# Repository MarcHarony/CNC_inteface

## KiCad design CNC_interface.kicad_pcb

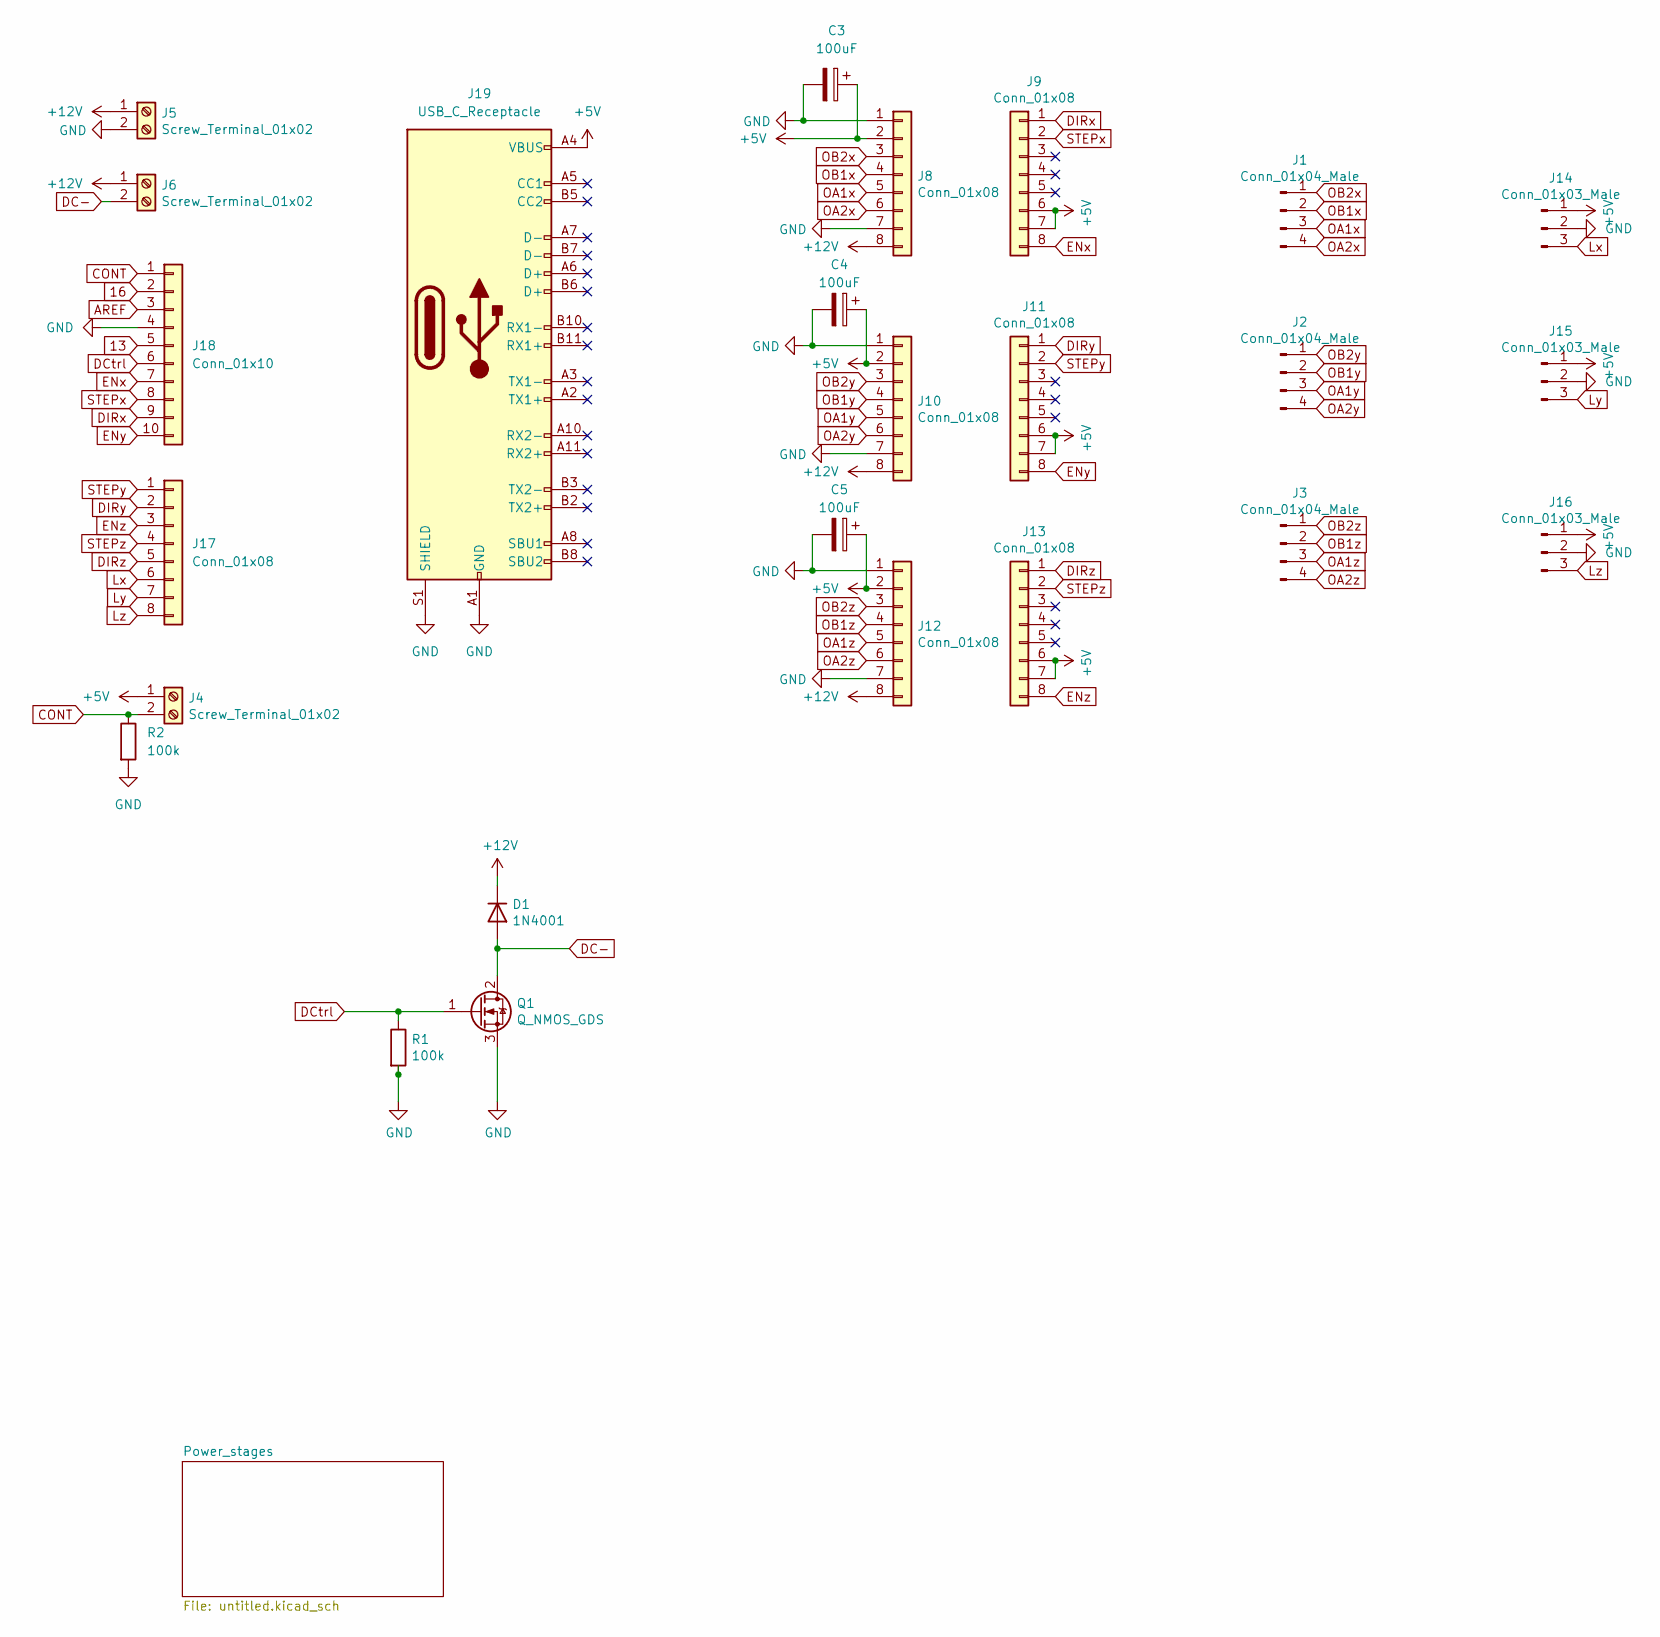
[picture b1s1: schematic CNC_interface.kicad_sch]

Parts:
C3, C4, C5: 100uF; CP_Radial_D6.3mm_P2.50mm
D1: 1N4001; D_DO-41_SOD81_P10.16mm_Horizontal
J1, J2, J3: Conn_01x04_Male; JST_XH_B4B-XH-A_1x04_P2.50mm_Vertical
J4, J5, J6: Screw_Terminal_01x02; RS_pro_screw_terminal_P5.08_x2
J8, J9, J10, J11, J12, J13: Conn_01x08; PinSocket_1x08_P2.54mm_Vertical
J14, J15, J16: Conn_01x03_Male; JST_XH_B3B-XH-A_1x03_P2.50mm_Vertical
J17: Conn_01x08; PinSocket_1x08_P2.54mm_Horizontal
J18: Conn_01x10; PinSocket_1x10_P2.54mm_Horizontal
J19: USB_C_Receptacle; USB_C_Receptacle_Amphenol_12401548E4-2A_CircularHoles
Q1: Q_NMOS_GDS; TO-220-3_Vertical
R1, R2: 100k; R_Axial_DIN0207_L6.3mm_D2.5mm_P10.16mm_Horizontal

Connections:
13: J18.5
16: J18.2
+5V: C3.1, C4.1, C5.1, J4.1, J8.2, J9.6, J9.7, J10.2, J11.6, J11.7, J12.2, J13.6, J13.7, J14.1, J15.1, J16.1, J19.A4 (VBUS), J19.A9 (VBUS), J19.B4 (VBUS), J19.B9 (VBUS); also elsewhere on the board
AREF: J18.3
CONT: J4.2, J18.1, R2.1
DC-: D1.2 (A), J6.2, Q1.2 (D)
DCtrl: J18.6, Q1.1 (G), R1.1
DIRx: J9.1, J18.9
DIRy: J11.1, J17.2
DIRz: J13.1, J17.5
ENx: J9.8, J18.7
ENy: J11.8, J18.10
ENz: J13.8, J17.3
GND: C3.2, C4.2, C5.2, J5.2, J8.1, J8.7, J10.1, J10.7, J12.1, J12.7, J14.2, J15.2, J16.2, J18.4, J19.A1 (GND), J19.A12 (GND), J19.B1 (GND), J19.B12 (GND), J19.S1 (SHIELD), Q1.3 (S), R1.2, R2.2; also elsewhere on the board
Lx: J14.3, J17.6
Ly: J15.3, J17.7
Lz: J16.3, J17.8
OA1x: J1.3, J8.5
OA1y: J2.3, J10.5
OA1z: J3.3, J12.5
OA2x: J1.4, J8.6
OA2y: J2.4, J10.6
OA2z: J3.4, J12.6
OB1x: J1.2, J8.4
OB1y: J2.2, J10.4
OB1z: J3.2, J12.4
OB2x: J1.1, J8.3
OB2y: J2.1, J10.3
OB2z: J3.1, J12.3
STEPx: J9.2, J18.8
STEPy: J11.2, J17.1
STEPz: J13.2, J17.4

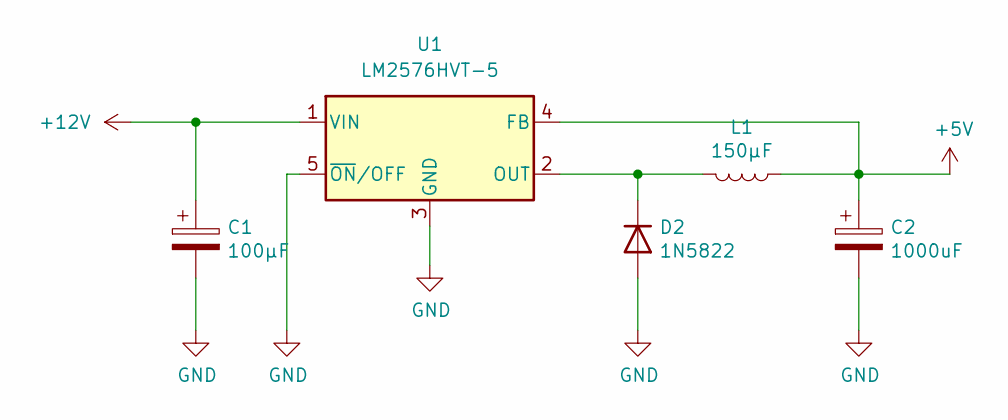
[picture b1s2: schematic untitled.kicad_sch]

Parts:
C1: 100µF; CP_Radial_D6.3mm_P2.50mm
C2: 1000uF; CP_Radial_D12.5mm_P5.00mm
D2: 1N5822; D_DO-201AD_P15.24mm_Horizontal
L1: 150µF; L_Radial_24.4mm_P23.50mm_Murata_1400series
U1: LM2576HVT-5; TO-220-5_Vertical

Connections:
+5V: C2.1, L1.1, U1.4 (FB); also elsewhere on the board
GND: C1.2, C2.2, D2.2 (A), U1.3 (GND), U1.5 (~ON/OFF); also elsewhere on the board
unnamed: D2.1 (K), L1.2, U1.2 (OUT)

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
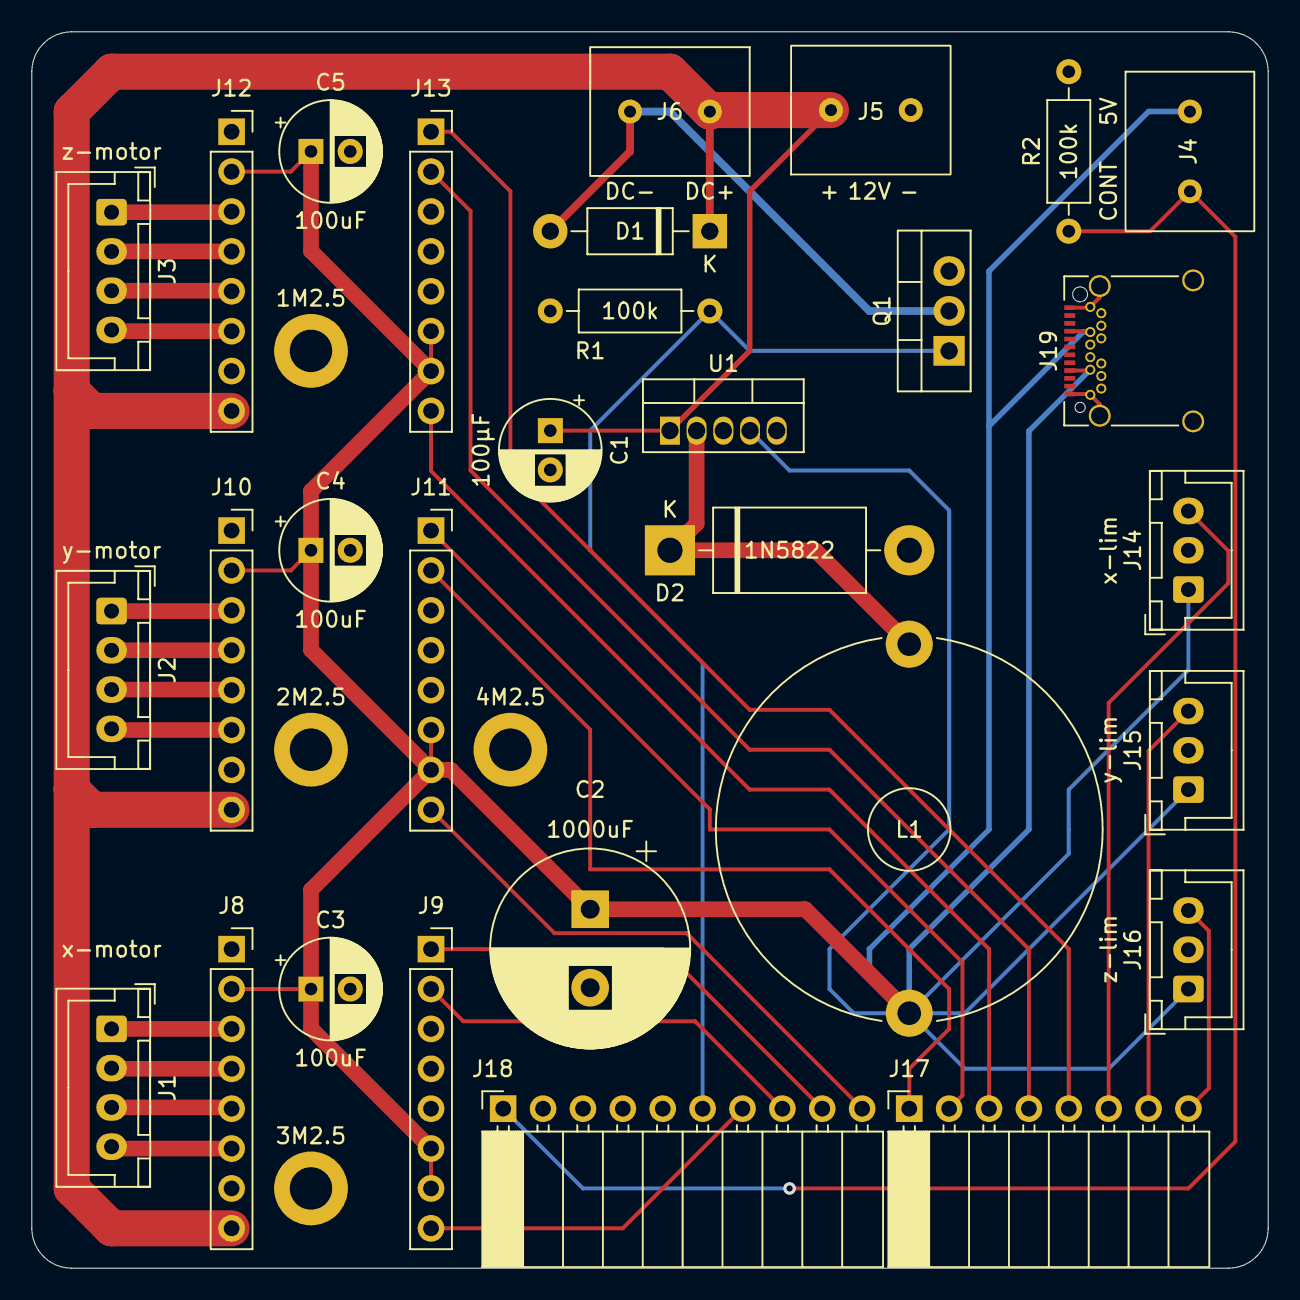
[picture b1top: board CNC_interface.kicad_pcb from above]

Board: 2 copper layers, 78.7 x 78.7 mm, 34 parts (0 on the bottom side), 31 nets.

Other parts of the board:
1M2.5, 2M2.5, 3M2.5, 4M2.5: MountingHole_2.7mm_M2.5_DIN965_Pad

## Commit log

2022-02-15 Initial version of CNC_interface
2022-02-15 adding capacitance footprints
2022-02-16 Groupage drivers
2022-02-16 Adding jumper Arduino
2022-02-16 Placing components on PCB
2022-02-17 wiring input to TMC
2022-02-18 debut seance
2022-02-18 Starting routing & adding capa
2022-02-18 Add 12V power stage
2022-02-18 Changing 12 to 24V
2022-02-18 add last footprints
2022-02-18 update component names
2022-02-22 Elements changed and routing
2022-02-22 Routing beside GND finished
2022-02-22 Create new design with LM2576
2022-02-22 replace LM2576 footprints
2022-02-22 Plan de masse
2022-02-22 Change discrete components
2022-02-22 place components on pcb
2022-02-23 place first traces
2022-02-23 route pcb + GND floorplan
2022-02-23 Finish routing
2022-02-23 connect step motors to 12V
2022-02-23 coolest branch in the forest
2022-02-23 place components
2022-02-23 Route PCB + silkscreen
2022-02-25 Finish pcb silkscreen and mounting pins
